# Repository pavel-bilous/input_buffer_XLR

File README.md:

# Input buffer for amplifier with balanced inputs

This buffer serves as an impedance matching and is implemented on the board that allows for balanced XLR inputs for two channels.

## PCB rendered in 3d:

## Schematics:

Opamps can be NE5532 or LM4562 or any other with good unity gain stability. 

Input XLR connectors are Neutrik NC3FAAH2.

Capacitors for input low pass filters are film type. Decoupling capacitors are X7R 100nF or higher (1uF will work great).

## PCB layout:

Bottom layer is GND. Top layer is signal + power and GND poured in between. Stiching vias are then applied to connect bottom and top GND planes to ensure those are as close to 0 as possible.

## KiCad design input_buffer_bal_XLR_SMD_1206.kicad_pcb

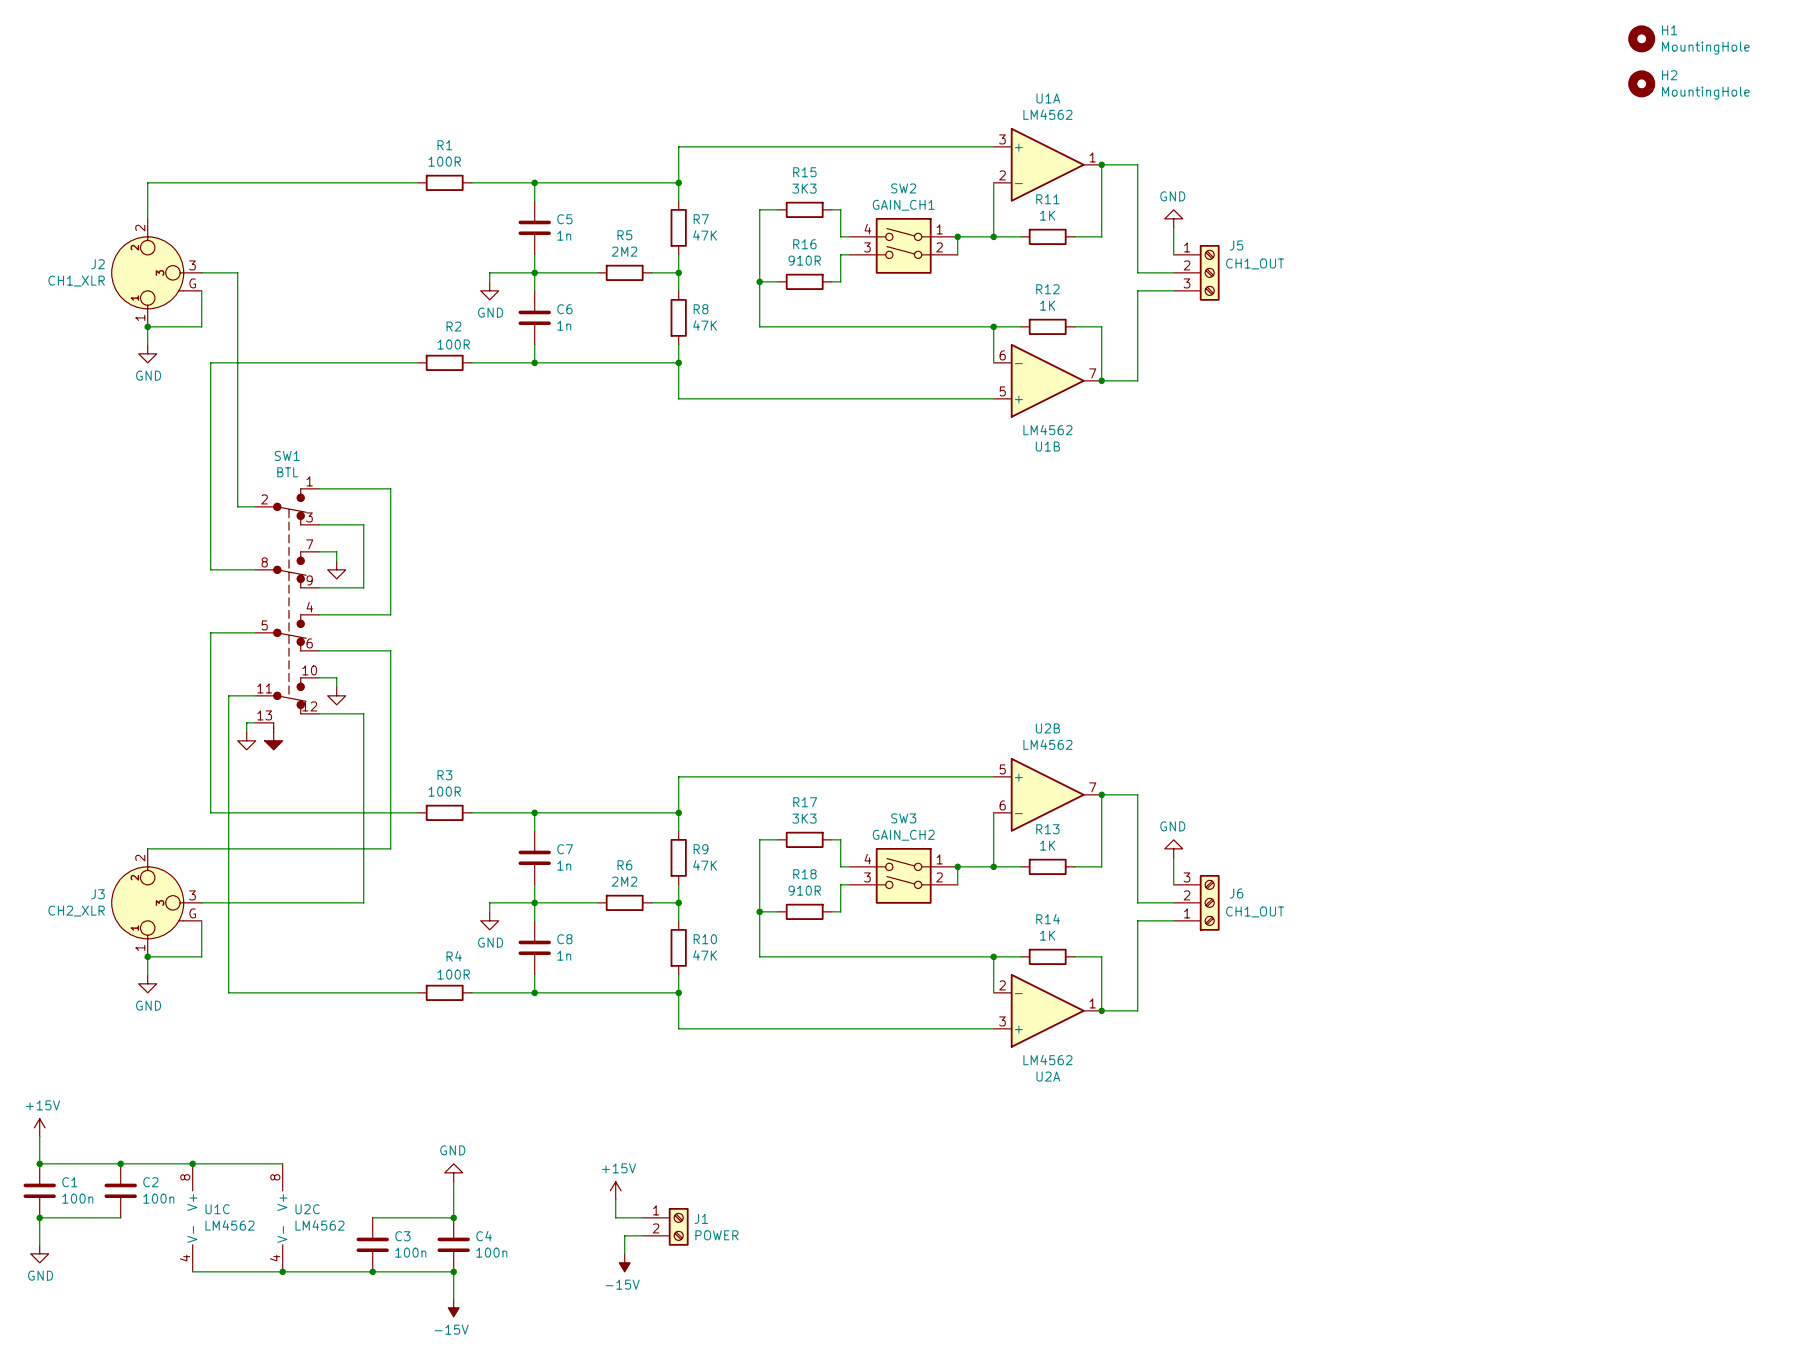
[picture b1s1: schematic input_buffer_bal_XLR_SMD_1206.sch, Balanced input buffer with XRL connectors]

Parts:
C1, C2, C3, C4: 100n; C_1206_3216Metric_Pad1.42x1.75mm_HandSolder
C5, C6, C7, C8: 1n; C_1206_3216Metric_Pad1.42x1.75mm_HandSolder
H1, H2: MountingHole; MountingHole_3.5mm_Pad_Via
J1: POWER; TerminalBlock_ Amphenol_01_02_P3.50mm
J2: CH1_XLR; Jack_XLR_Neutrik_NC3FAAH2_Horizontal_centered
J3: CH2_XLR; Jack_XLR_Neutrik_NC3FAAH2_Horizontal_centered
J5, J6: CH1_OUT; TerminalBlock_ Amphenol_01_03_P3.50mm
R1, R2, R3, R4: 100R; R_1206_3216Metric
R5, R6: 2M2; R_1206_3216Metric
R7, R8, R9, R10: 47K; R_1206_3216Metric
R11, R12, R13, R14: 1K; R_1206_3216Metric
R15, R17: 3K3; R_1206_3216Metric
R16, R18: 910R; R_1206_3216Metric
SW1: BTL; SW_SS-42H11_4PDT
SW2: GAIN_CH1; SW_DIP_SPSTx02_Slide_W7.62mm_P2.54mm
SW3: GAIN_CH2; SW_DIP_SPSTx02_Slide_W7.62mm_P2.54mm
U1, U2: LM4562; SOIC-8_3.9x4.9mm_P1.27mm

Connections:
+15V: C1.1, C2.1, J1.1, U1.8 (V+), U2.8 (V+)
-15V: C3.2, C4.2, J1.2, U1.4 (V-), U2.4 (V-)
GND: C1.2, C2.2, C3.1, C4.1, C5.2, C6.1, C7.2, C8.1, J2.1, J2.G, J3.1, J3.G, J5.1, J6.3, R5.2, R6.2, SW1.7 (A), SW1.10 (A), SW1.13 (GND)
unnamed: C5.1, R1.1, R7.1, U1.3 (+)
unnamed: C6.2, R2.1, R8.2, U1.5 (+)
unnamed: C7.1, R3.1, R9.1, U2.5 (+)
unnamed: C8.2, R4.1, R10.2, U2.3 (+)
unnamed: J2.2, R1.2
unnamed: J2.3, SW1.2 (B)
unnamed: J3.2, SW1.6 (C)
unnamed: J3.3, SW1.12 (C)
unnamed: J5.2, R11.1, U1.1
unnamed: J5.3, R12.1, U1.7
unnamed: J6.1, R14.1, U2.1
unnamed: J6.2, R13.1, U2.7
unnamed: R2.2, SW1.8 (B)
unnamed: R3.2, SW1.5 (B)
unnamed: R4.2, SW1.11 (B)
unnamed: R5.1, R7.2, R8.1
unnamed: R6.1, R9.2, R10.1
unnamed: R11.2, SW2.1, SW2.2, U1.2 (-)
unnamed: R12.2, R15.1, R16.1, U1.6 (-)
unnamed: R13.2, SW3.1, SW3.2, U2.6 (-)
unnamed: R14.2, R17.1, R18.1, U2.2 (-)
unnamed: R15.2, SW2.4
unnamed: R16.2, SW2.3
unnamed: R17.2, SW3.4
unnamed: R18.2, SW3.3
unnamed: SW1.1 (A), SW1.4 (A)
unnamed: SW1.3 (C), SW1.9 (C)

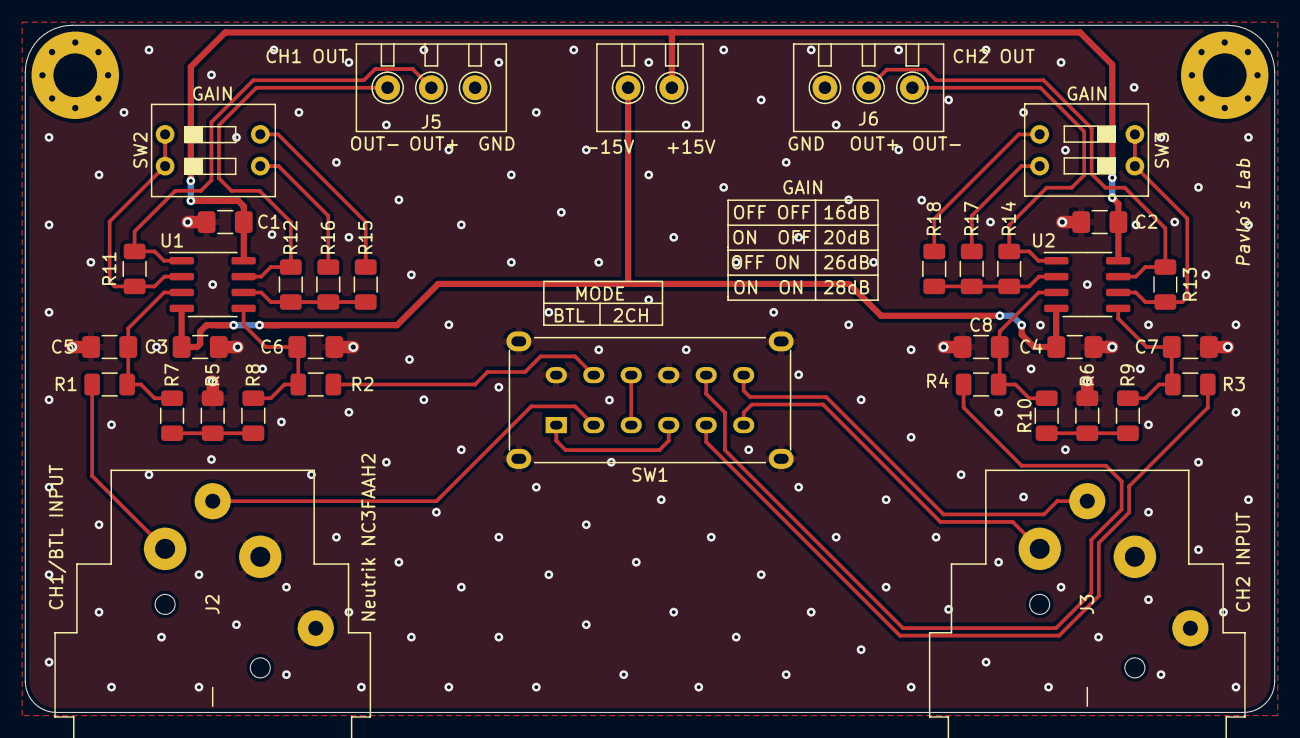
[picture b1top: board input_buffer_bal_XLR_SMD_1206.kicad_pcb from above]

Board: 2 copper layers, 100.0 x 55.0 mm, 38 parts (0 on the bottom side), 30 nets.

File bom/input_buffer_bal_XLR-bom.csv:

"Id";"Designator";"Package";"Quantity";"Designation";"Supplier and ref";
1;"H2,H1";"MountingHole_3.5mm_Pad_Via";2;"MountingHole";;;
2;"U2,U1";"DIP-8_W7.62mm_centered";2;"LM4562";;;
3;"R10,R9,R8,R7";"R_Axial_DIN0207_L6.3mm_D2.5mm_P10.16mm_Horizontal_centered";4;"47K";;;
4;"R6,R5";"R_Axial_DIN0207_L6.3mm_D2.5mm_P10.16mm_Horizontal_centered";2;"2M2";;;
5;"R4,R3,R2,R1";"R_Axial_DIN0207_L6.3mm_D2.5mm_P10.16mm_Horizontal_centered";4;"100R";;;
6;"J2";"Jack_XLR_Neutrik_NC3FAAH2_Horizontal_centered";1;"CH2_XLR";;;
7;"J1";"Jack_XLR_Neutrik_NC3FAAH2_Horizontal_centered";1;"CH1_XLR";;;
8;"D4,D3,D2,D1";"D_DO-15_P12.70mm_Horizontal_centered_TVS";4;"P6KE6.8";;;
9;"C8,C7,C6,C5";"C_Disc_D3.8mm_W2.6mm_P2.50mm_centered";4;"220p";;;
10;"C4,C3,C2,C1";"C_Disc_D3.8mm_W2.6mm_P2.50mm_centered";4;"100n";;;
11;"J5";"TerminalBlock_ Amphenol_01_03_P3.50mm";1;"CH2_OUT";;;
12;"J4";"TerminalBlock_ Amphenol_01_03_P3.50mm";1;"CH1_OUT";;;
13;"J3";"TerminalBlock_ Amphenol_01_03_P3.50mm";1;"POWER";;;

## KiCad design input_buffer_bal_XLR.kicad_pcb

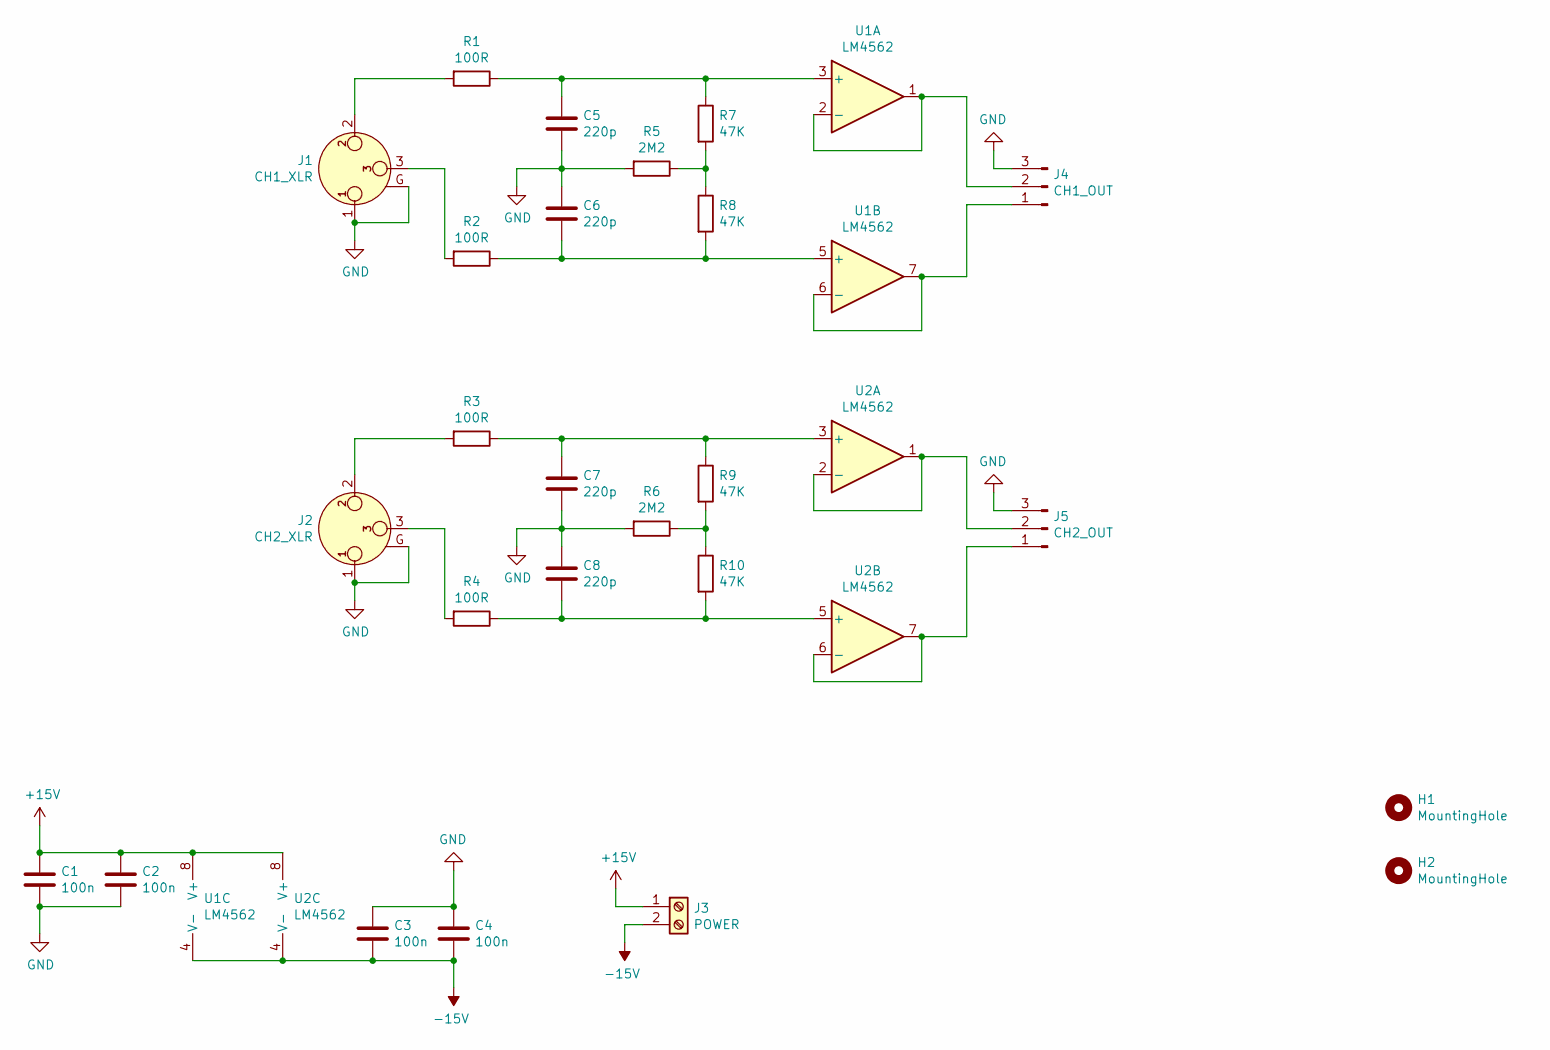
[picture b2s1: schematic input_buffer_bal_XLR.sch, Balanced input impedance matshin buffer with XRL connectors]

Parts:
C1, C2, C3, C4: 100n; C_Disc_D3.8mm_W2.6mm_P2.50mm_centered
C5, C6, C7, C8: 220p; C_Rect_L7.2mm_W4.5mm_P5.00mm_FKS2_FKP2_MKS2_MKP2
H1, H2: MountingHole; MountingHole_3.5mm_Pad_Via
J1: CH1_XLR; Jack_XLR_Neutrik_NC3FAAH2_Horizontal_centered
J2: CH2_XLR; Jack_XLR_Neutrik_NC3FAAH2_Horizontal_centered
J3: POWER; TerminalBlock_ Amphenol_01_02_P3.50mm
J4: CH1_OUT; TerminalBlock_ Amphenol_01_03_P3.50mm
J5: CH2_OUT; TerminalBlock_ Amphenol_01_03_P3.50mm
R1, R2, R3, R4: 100R; R_Axial_DIN0207_L6.3mm_D2.5mm_P10.16mm_Horizontal_centered
R5, R6: 2M2; R_Axial_DIN0207_L6.3mm_D2.5mm_P10.16mm_Horizontal_centered
R7, R8, R9, R10: 47K; R_Axial_DIN0207_L6.3mm_D2.5mm_P10.16mm_Horizontal_centered
U1, U2: LM4562; DIP-8_W7.62mm_centered

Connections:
+15V: C1.1, C2.1, J3.1, U1.8 (V+), U2.8 (V+)
-15V: C3.2, C4.2, J3.2, U1.4 (V-), U2.4 (V-)
GND: C1.2, C2.2, C3.1, C4.1, C5.2, C6.1, C7.2, C8.1, J1.1, J1.G, J2.1, J2.G, J4.3, J5.3, R5.2, R6.2
unnamed: C5.1, R1.1, R7.1, U1.3 (+)
unnamed: C6.2, R2.1, R8.2, U1.5 (+)
unnamed: C7.1, R3.1, R9.1, U2.3 (+)
unnamed: C8.2, R4.1, R10.2, U2.5 (+)
unnamed: J1.2, R1.2
unnamed: J1.3, R2.2
unnamed: J2.2, R3.2
unnamed: J2.3, R4.2
unnamed: J4.1, U1.6 (-), U1.7
unnamed: J4.2, U1.1, U1.2 (-)
unnamed: J5.1, U2.6 (-), U2.7
unnamed: J5.2, U2.1, U2.2 (-)
unnamed: R5.1, R7.2, R8.1
unnamed: R6.1, R9.2, R10.1

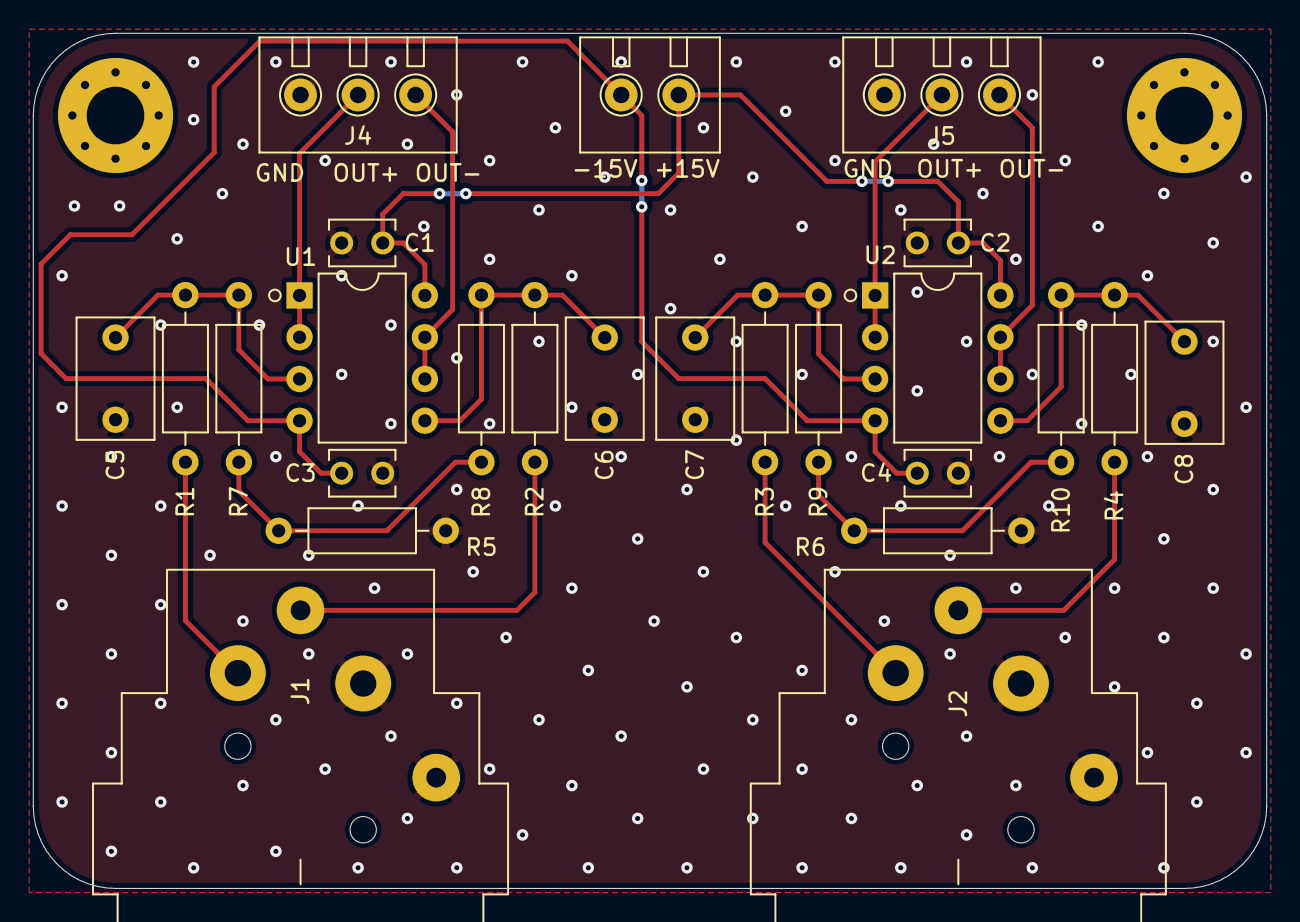
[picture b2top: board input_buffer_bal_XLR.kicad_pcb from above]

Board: 2 copper layers, 75.0 x 52.0 mm, 27 parts (0 on the bottom side), 17 nets.

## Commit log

2023-04-17 added project files
2023-05-06 rev1.1 fixes major issues with the pcb layout
2023-05-06 updated pos files
2023-05-06 updated gerber files
2023-05-06 rev1.1 fixes major issues with the layout
2023-05-06 updates to film caps
2023-06-01 rev1.2
2023-06-01 rev1.2 changed power connector
2024-01-06 revised with added option to change gain
2024-01-06 readme update
2024-01-06 grb updated
2024-01-06 updated to r2.0
2024-01-09 added bom
2024-01-19 footprints updates
2024-01-20 finished layout
2024-01-20 updated gerbers
